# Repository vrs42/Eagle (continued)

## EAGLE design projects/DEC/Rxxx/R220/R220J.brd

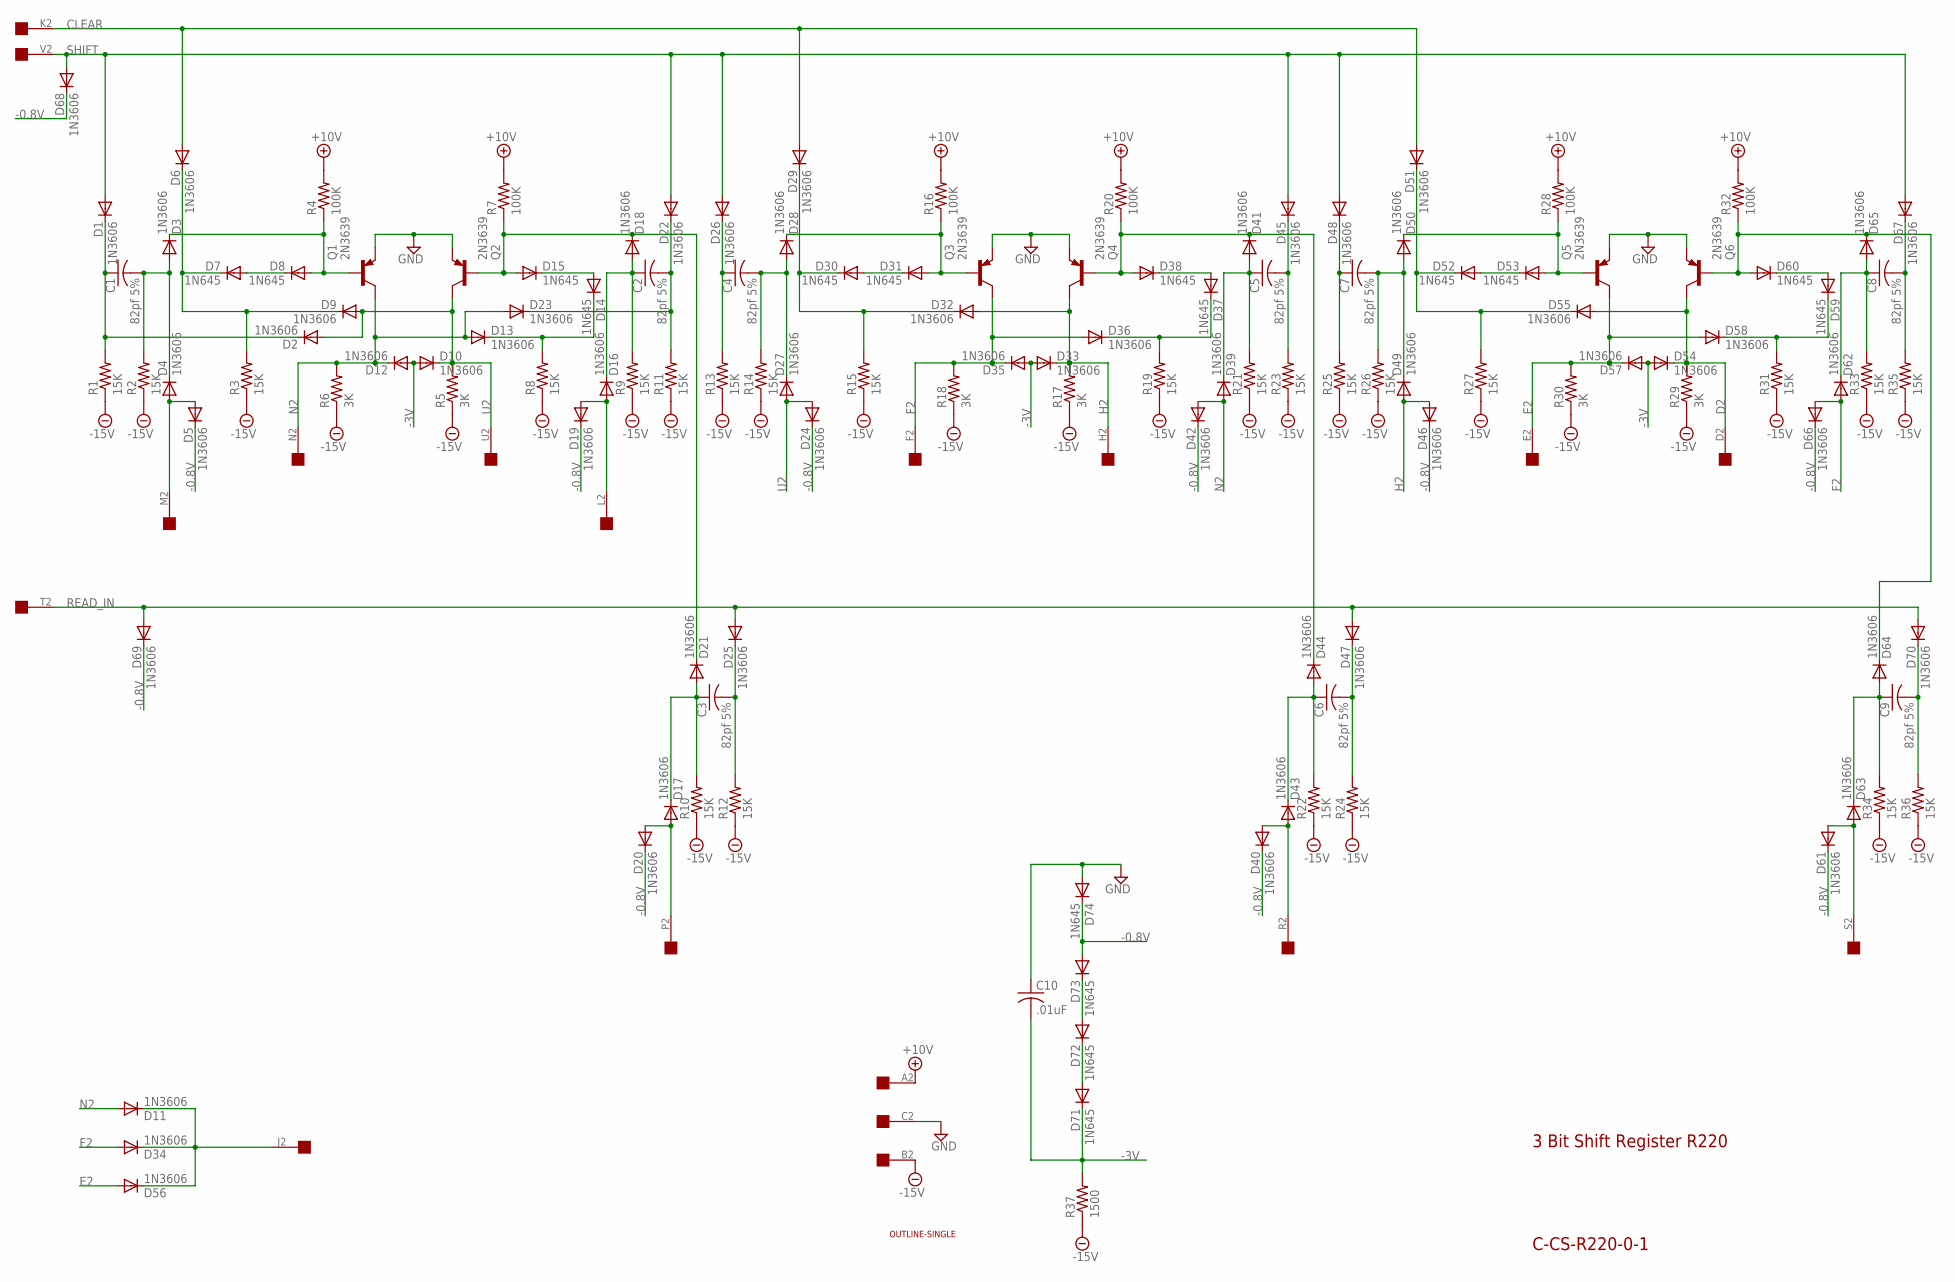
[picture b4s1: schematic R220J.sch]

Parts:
C1, C2, C3, C4, C5, C6, C7, C8, C9: 82pf 5%; C050-025X075
C10: .01uF; C050-025X075
D1, D2, D3, D4, D5, D6, D9, D10, D11, D12, D13, D16, D17, D18, D19, D20, D21, D22, D23, D24, D25, D26, D27, D28, D29, D32, D33, D34, D35, D36, D39, D40, D41, D42, D43, D44, D45, D46, D47, D48, D49, D50, D51, D54, D55, D56, D57, D58, D61, D62, D63, D64, D65, D66, D67, D68, D69, D70: 1N3606; DO35-10
D7, D8, D14, D15, D30, D31, D37, D38, D52, D53, D59, D60, D71, D72, D73, D74: 1N645; DO35-10
Q1, Q2, Q3, Q4, Q5, Q6: 2N3639; TO39
R1, R2, R3, R8, R9, R10, R11, R12, R13, R14, R15, R19, R21, R22, R23, R24, R25, R26, R27, R31, R33, R34, R35, R36: 15K; 0207/10
R4, R7, R16, R20, R28, R32: 100K; 0207/10
R5, R6, R17, R18, R29, R30: 3K; 0207/10
R37: 1500; 0207/10
U$1: OUTLINE-SINGLE; SINGLE
U$2: EDGE-1; EDGE-CON1

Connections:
+10V: R4.2, R7.2, R16.2, R20.2, R28.2, R32.2, U$2.A2
-0.8V: D5.C, D19.C, D20.C, D24.C, D40.C, D42.C, D46.C, D61.C, D66.C, D68.C, D69.C, D73.A, D74.C
-3V: C10.2, D10.A, D12.A, D33.A, D35.A, D54.A, D57.A, D71.C, R37.2
-15V: R1.1, R2.1, R3.1, R5.1, R6.1, R8.1, R9.1, R10.1, R11.1, R12.1, R13.1, R14.1, R15.1, R17.1, R18.1, R19.1, R21.1, R22.1, R23.1, R24.1, R25.1, R26.1, R27.1, R29.1, R30.1, R31.1, R33.1, R34.1, R35.1, R36.1, R37.1, U$2.B2
CLEAR: D6.A, D29.A, D51.A, U$2.K2
D2: D54.C, D55.A, Q6.3 (C), R29.2, U$2.D2
E2: D56.A, D57.C, D58.A, Q5.3 (C), R30.2, U$2.E2
F2: D34.A, D35.C, D36.A, D62.A, D66.A, Q3.3 (C), R18.2, U$2.F2
GND: C10.1, D74.A, Q1.1 (E), Q2.1 (E), Q3.1 (E), Q4.1 (E), Q5.1 (E), Q6.1 (E), U$2.C2
H2: D32.A, D33.C, D46.A, D49.A, Q4.3 (C), R17.2, U$2.H2
N2: D11.A, D12.C, D13.A, D23.A, D39.A, D42.A, Q1.3 (C), R6.2, U$2.N2
unnamed: D30.A, D31.C
unnamed: C2.2, D22.C, D23.C, R11.2
unnamed: D29.C, D30.C, D32.C, R15.2
unnamed: C1.1, D1.C, D2.C, R1.2
unnamed: D14.A, D15.C
unnamed: C1.2, D3.A, D4.C, R2.2
unnamed: C2.1, D16.C, D18.A, R9.2
unnamed: D6.C, D7.C, D9.C, R3.2
unnamed: D4.A, D5.A, U$2.M2
unnamed: D28.C, D31.A, Q3.2 (B), R16.1
unnamed: D13.C, D14.C, R8.2
unnamed: D37.A, D38.C
unnamed: D3.C, D8.A, Q1.2 (B), R4.1
unnamed: D38.A, D41.C, D44.C, Q4.2 (B), R20.1
unnamed: D36.C, D37.C, R19.2
unnamed: D15.A, D18.C, D21.C, Q2.2 (B), R7.1
unnamed: C4.1, D26.C, R13.2
unnamed: C4.2, D27.C, D28.A, R14.2
unnamed: C5.1, D39.C, D41.A, R21.2
unnamed: D7.A, D8.C
unnamed: D11.C, D34.C, D56.C, U$2.J2
unnamed: C5.2, D45.C, R23.2
unnamed: D52.A, D53.C
unnamed: D51.C, D52.C, D55.C, R27.2
unnamed: D50.C, D53.A, Q5.2 (B), R28.1
unnamed: D59.A, D60.C
unnamed: D60.A, D64.C, D65.C, Q6.2 (B), R32.1
unnamed: D16.A, D19.A, U$2.L2
unnamed: D58.C, D59.C, R31.2
unnamed: C7.1, D48.C, R25.2
unnamed: C7.2, D49.C, D50.A, R26.2
unnamed: D71.A, D72.C
unnamed: C8.1, D62.C, D65.A, R33.2
unnamed: C8.2, D67.C, R35.2
unnamed: D72.A, D73.C
unnamed: C3.1, D17.C, D21.A, R10.2
unnamed: C3.2, D25.C, R12.2
unnamed: C6.1, D43.C, D44.A, R22.2
unnamed: C6.2, D47.C, R24.2
unnamed: C9.1, D63.C, D64.A, R34.2
unnamed: C9.2, D70.C, R36.2
P2: D17.A, D20.A, U$2.P2
R2: D40.A, D43.A, U$2.R2
READ_IN: D25.A, D47.A, D69.A, D70.A, U$2.T2
S2: D61.A, D63.A, U$2.S2
SHIFT: D1.A, D22.A, D26.A, D45.A, D48.A, D67.A, D68.A, U$2.V2
U2: D2.A, D9.A, D10.C, D24.A, D27.A, Q2.3 (C), R5.2, U$2.U2

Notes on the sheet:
3 Bit Shift Register R220
C-CS-R220-0-1

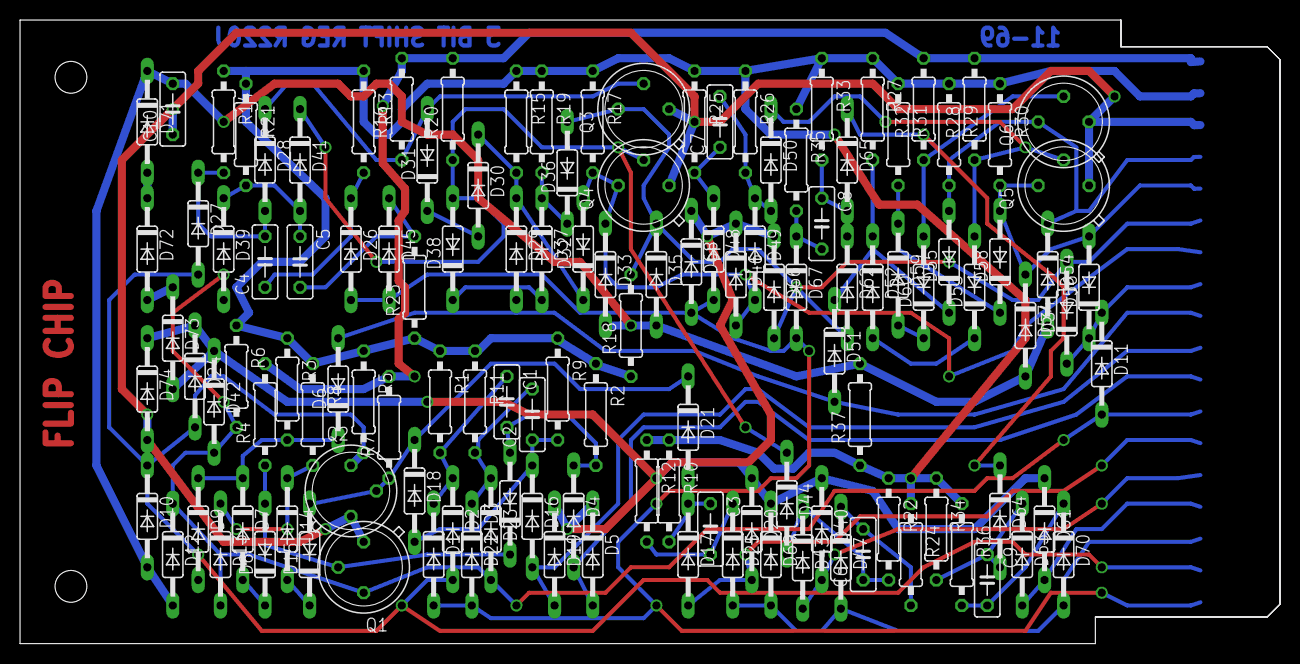
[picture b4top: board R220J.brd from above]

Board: 2 copper layers, 125.7 x 62.2 mm, 130 parts (0 on the bottom side), 58 nets.

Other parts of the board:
U$3: FLIPCHIP
